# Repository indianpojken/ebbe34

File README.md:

# ebbe34

**ebbe34** is a minimalist, ergonomic 34-key keyboard designed with portability in mind. It features a unibody layout, hot-swappable sockets compatible with Kailh Choc V1 and V2 low-profile switches, and nice!view display — powered by the nice!nano controller.

---

## 🧩 Parts Required

- **1×** nice!nano V2
- **1×** nice!view display
- **1×** Li-Po Battery 301230 (110 mAh)
- **1×** 2-pin THT Reset Switch
- **34×** Kailh Choc V1 or V2 Hotswap Sockets
- **34×** 1N4148W SMD Diodes
- **1x** MSK12C02 Power Switch

All required parts are available from [42keebs.eu](https://42keebs.eu).

---

## 🛠 Firmware

You can find the firmware [here](https://github.com/indianpojken/ebbe34-zmk).

---

## 📸 Images

_Built from revision `6ba714b`_

---

## 🙌 Credits

Inspiration and footprints from:

- [Urchin by duckyb](https://github.com/duckyb/urchin)
- [ScottoKeebs by joe-scotto](https://github.com/joe-scotto/scottokeebs/tree/main/Extras/ScottoKicad)

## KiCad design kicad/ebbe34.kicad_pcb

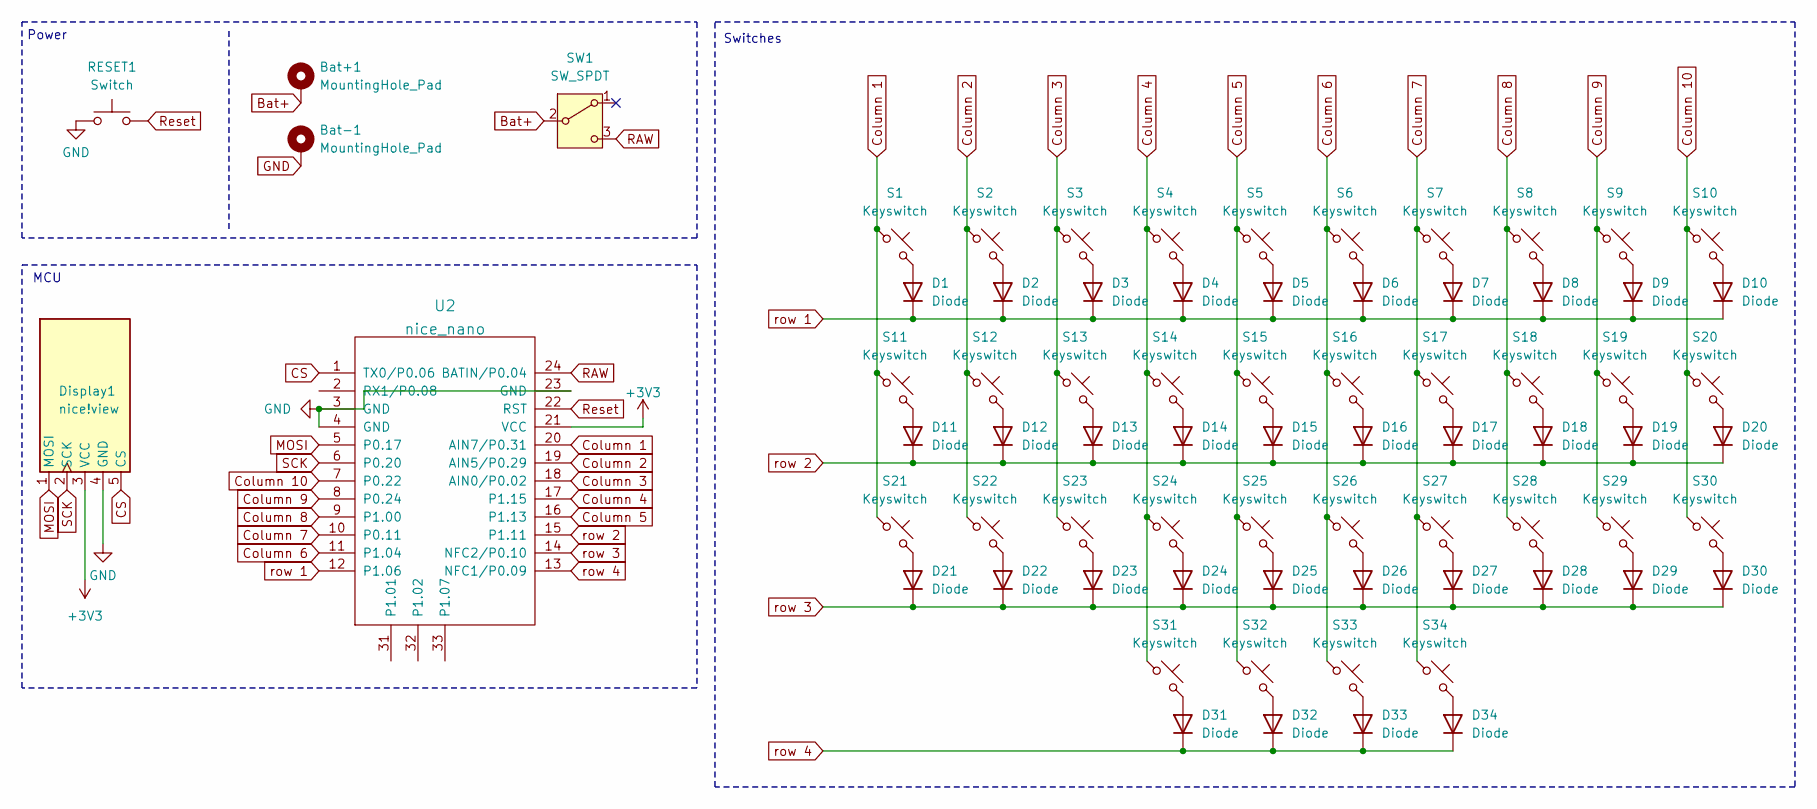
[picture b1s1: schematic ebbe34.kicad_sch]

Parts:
Bat+1: MountingHole_Pad; Battery+
Bat-1: MountingHole_Pad; Battery-
D1, D2, D3, D4, D5, D6, D7, D8, D9, D10, D11, D12, D13, D14, D15, D16, D17, D18, D19, D20, D21, D22, D23, D24, D25, D26, D27, D28, D29, D30, D31, D32, D33, D34: Diode; SMD_Diode_Tiny_dual_layer
Display1: nice!view; nice_view
RESET1: Switch; Button_MJTP1243
S1, S2, S3, S4, S5, S6, S7, S8, S9, S10, S11, S12, S13, S14, S15, S16, S17, S18, S19, S20, S21, S22, S23, S24, S25, S26, S27, S28, S29, S30, S31, S32, S33, S34: Keyswitch; Hotswap_Choc_V1V2
SW1: SW_SPDT; Switch_MSK12C02
U2: nice_nano

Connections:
+3V3: Display1.3 (VCC), U2.21 (VCC)
Bat+: Bat+1.1, SW1.2 (B)
CS: Display1.5 (CS), U2.1 (TX0/P0.06)
Column 1: S1.1, S11.1, S21.1, U2.20 (AIN7/P0.31)
Column 2: S2.1, S12.1, S22.1, U2.19 (AIN5/P0.29)
Column 3: S3.1, S13.1, S23.1, U2.18 (AIN0/P0.02)
Column 4: S4.1, S14.1, S24.1, S31.1, U2.17 (P1.15)
Column 5: S5.1, S15.1, S25.1, S32.1, U2.16 (P1.13)
Column 6: S6.1, S16.1, S26.1, S33.1, U2.11 (P1.04)
Column 7: S7.1, S17.1, S27.1, S34.1, U2.10 (P0.11)
Column 8: S8.1, S18.1, S28.1, U2.9 (P1.00)
Column 9: S9.1, S19.1, S29.1, U2.8 (P0.24)
Column 10: S10.1, S20.1, S30.1, U2.7 (P0.22)
GND: Bat-1.1, Display1.4 (GND), RESET1.1, U2.3 (GND), U2.4 (GND), U2.23 (GND)
MOSI: Display1.1 (MOSI), U2.5 (P0.17)
unnamed: D1.2 (A), S1.2
unnamed: D2.2 (A), S2.2
unnamed: D3.2 (A), S3.2
unnamed: D4.2 (A), S4.2
unnamed: D5.2 (A), S5.2
unnamed: D6.2 (A), S6.2
unnamed: D7.2 (A), S7.2
unnamed: D8.2 (A), S8.2
unnamed: D9.2 (A), S9.2
unnamed: D10.2 (A), S10.2
unnamed: D11.2 (A), S11.2
unnamed: D12.2 (A), S12.2
unnamed: D13.2 (A), S13.2
unnamed: D14.2 (A), S14.2
unnamed: D15.2 (A), S15.2
unnamed: D16.2 (A), S16.2
unnamed: D17.2 (A), S17.2
unnamed: D18.2 (A), S18.2
unnamed: D19.2 (A), S19.2
unnamed: D20.2 (A), S20.2
unnamed: D21.2 (A), S21.2
unnamed: D22.2 (A), S22.2
unnamed: D23.2 (A), S23.2
unnamed: D24.2 (A), S24.2
unnamed: D25.2 (A), S25.2
unnamed: D26.2 (A), S26.2
unnamed: D27.2 (A), S27.2
unnamed: D28.2 (A), S28.2
unnamed: D29.2 (A), S29.2
unnamed: D30.2 (A), S30.2
unnamed: D31.2 (A), S31.2
unnamed: D32.2 (A), S32.2
unnamed: D33.2 (A), S33.2
unnamed: D34.2 (A), S34.2
RAW: SW1.3 (C), U2.24 (BATIN/P0.04)
Reset: RESET1.2, U2.22 (RST)
SCK: Display1.2 (SCK), U2.6 (P0.20)
row 1: D1.1 (K), D2.1 (K), D3.1 (K), D4.1 (K), D5.1 (K), D6.1 (K), D7.1 (K), D8.1 (K), D9.1 (K), D10.1 (K), U2.12 (P1.06)
row 2: D11.1 (K), D12.1 (K), D13.1 (K), D14.1 (K), D15.1 (K), D16.1 (K), D17.1 (K), D18.1 (K), D19.1 (K), D20.1 (K), U2.15 (P1.11)
row 3: D21.1 (K), D22.1 (K), D23.1 (K), D24.1 (K), D25.1 (K), D26.1 (K), D27.1 (K), D28.1 (K), D29.1 (K), D30.1 (K), U2.14 (NFC2/P0.10)
row 4: D31.1 (K), D32.1 (K), D33.1 (K), D34.1 (K), U2.13 (NFC1/P0.09)

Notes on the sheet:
Power
MCU
Switches

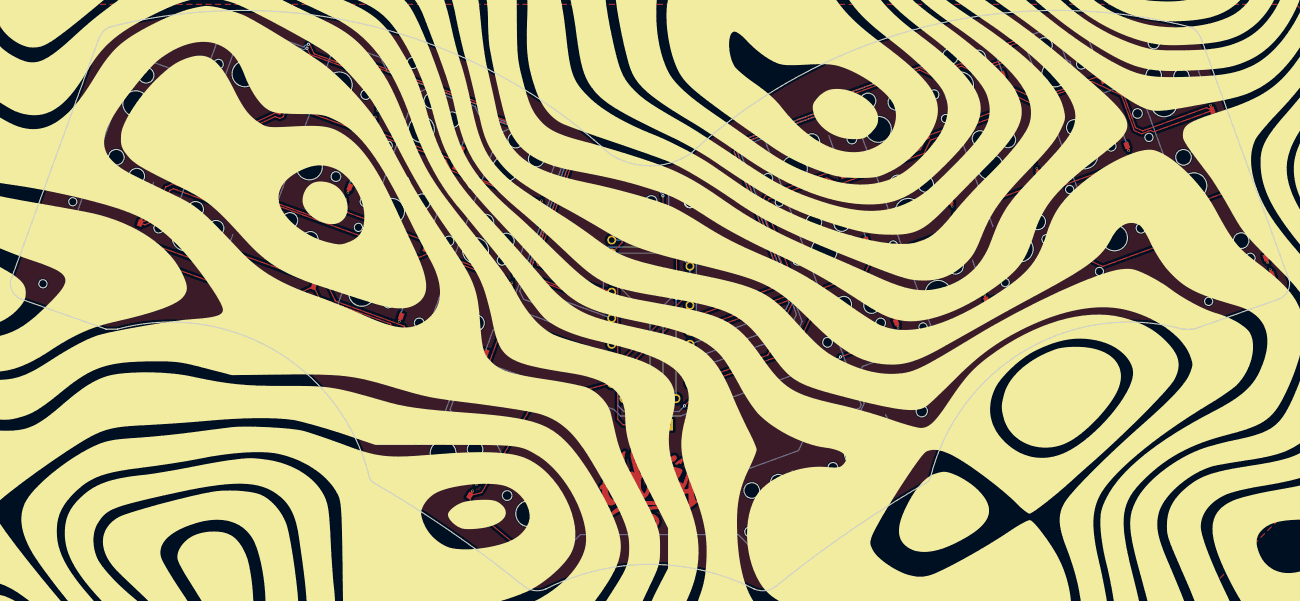
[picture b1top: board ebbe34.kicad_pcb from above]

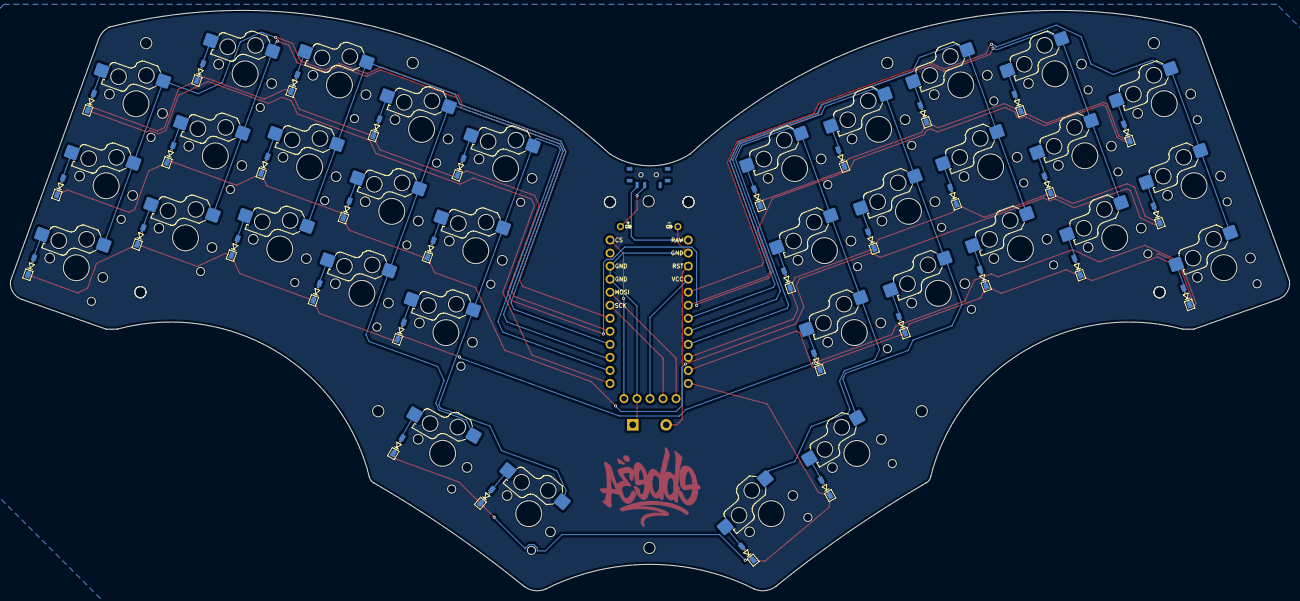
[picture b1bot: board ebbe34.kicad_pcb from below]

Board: 2 copper layers, 249.3 x 113.1 mm, 74 parts (36 on the bottom side), 56 nets.

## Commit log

2025-05-25 initial
2025-05-25 add power switch
2025-05-26 fix: move reset switch and tweak top plate
2025-05-28 add screen cover
2025-06-07 redo outline
2025-06-12 move screws
2025-06-13 restore bottom curvature
2025-06-29 Add missing part.
